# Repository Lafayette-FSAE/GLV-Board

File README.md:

# GLV-Board
Old Rev 4 of GLV Board

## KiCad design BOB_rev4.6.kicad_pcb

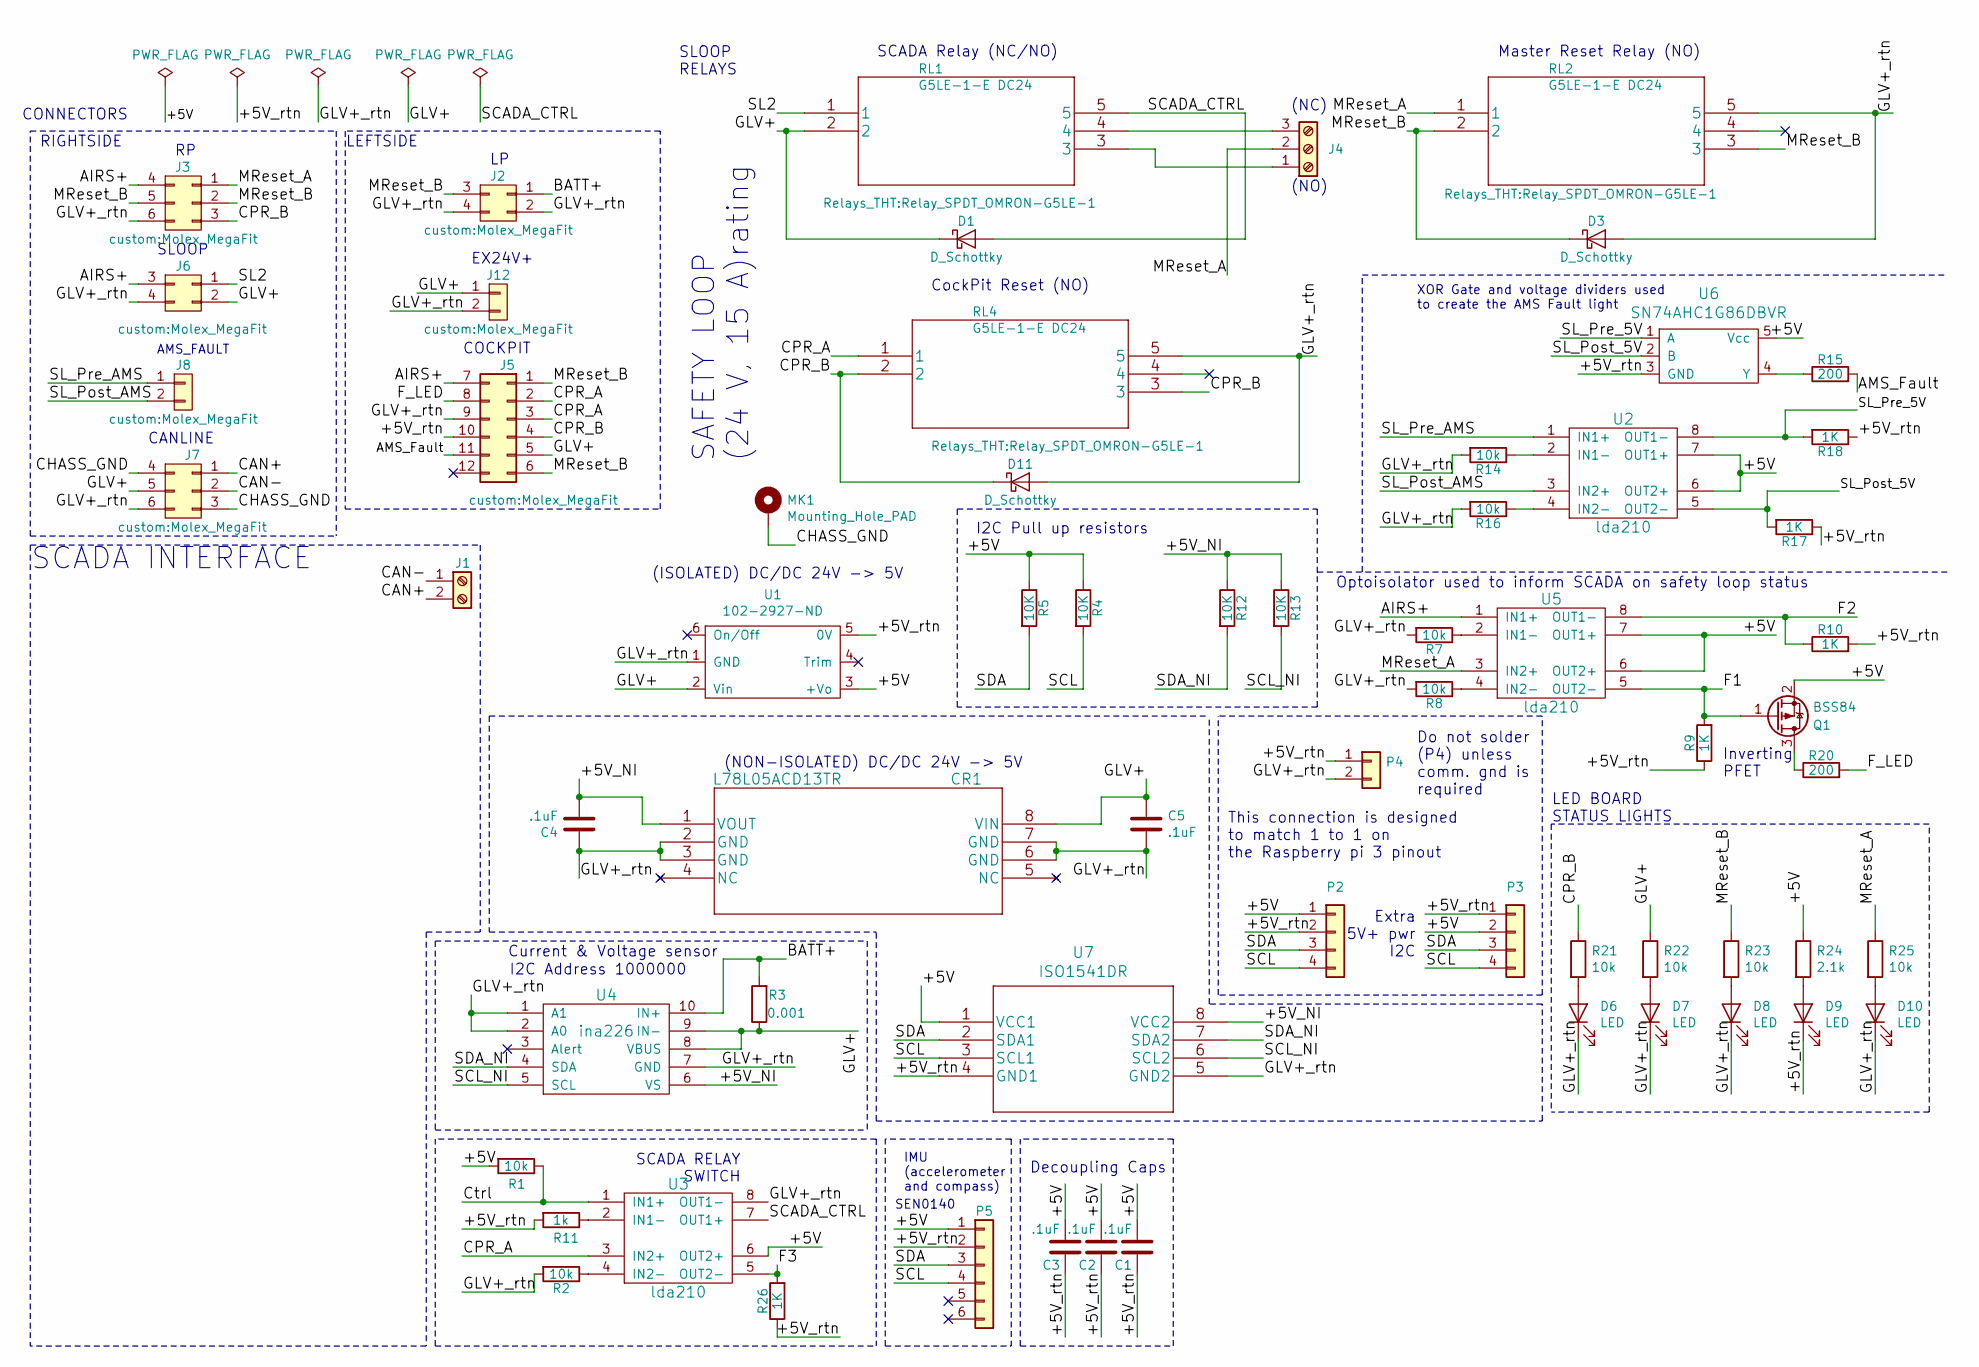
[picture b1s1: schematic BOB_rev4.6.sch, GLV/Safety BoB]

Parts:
C1, C2, C3, C4, C5: .1uF; C_0805_HandSoldering
CR1: L78L05ACD13TR
D1, D3, D11: D_Schottky; D_SMA_Handsoldering
D6, D7, D8, D9, D10: LED; LED_0805
J1: CONN_01X02; TerminalBlock_Pheonix_MPT-5.08mm_2pol
J2: Conn_02x02; Molex_MegaFit
J3: CONN_02X03; Molex_MegaFit
J4: CONN_01X03
J5: CONN_02X06-conn; Molex_MegaFit
J6, J7: Conn_02x03; Molex_MegaFit
J8, J12: Conn_01x02; Molex_MegaFit
MK1: Mounting_Hole_PAD; MountingHole_2.5mm_Pad
P2, P3, P5: CONN_01X04; Socket_Strip_Straight_1x04_Pitch2.54mm
P4: CONN_01X02; Socket_Strip_Straight_2x01_Pitch2.54mm
Q1: BSS84; SOT-23
R1, R2, R7, R8, R14, R16, R21, R22, R23, R25: 10k; R_0805_HandSoldering
R3: 0.001; R_0805_HandSoldering
R4, R5, R12, R13: 10K; R_0805_HandSoldering
R9, R10, R17, R18, R26: 1K; R_0805_HandSoldering
R11: 1k; R_0805_HandSoldering
R15, R20: 200; R_0805_HandSoldering
R24: 2.1k; R_0805_HandSoldering
RL1, RL2, RL4: G5LE-1-E DC24; Relay_SPDT_OMRON-G5LE-1
U1: 102-2927-ND
U2, U3, U5: lda210; DIP-8_W7.62mm
U4: ina226; msop_10_ads1015
U6: SN74AHC1G86DBVR; SOT-23-5_HandSoldering
U7: ISO1541DR

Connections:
/+5V: C1.2, C2.2, C3.2, P2.1, P3.2, P5.1, Q1.2 (S), R1.2, R4.1, R5.1, R24.1, U1.3 (+Vo), U2.6 (OUT2+), U2.7 (OUT1+), U3.6 (OUT2+), U5.6 (OUT2+), U5.7 (OUT1+), U6.5 (Vcc), U7.1 (VCC1)
/+5V_NI: C4.2, CR1.1 (VOUT), R12.1, R13.1, U4.6 (VS), U7.8 (VCC2)
/+5V_rtn: C1.1, C2.1, C3.1, D9.1 (K), J5.10, P2.2, P3.1, P4.1, P5.2, R9.1, R10.2, R11.2, R17.1, R18.1, R26.1, U1.5 (0V), U6.3 (GND), U7.4 (GND1)
/AIRS+: J3.4, J5.7, J6.3, U5.1 (IN1+)
/AMS_Fault: J5.11, R15.2
/BATT+: J2.1, R3.2, U4.10 (IN+)
/CAN+: J1.2, J7.1
/CAN-: J1.1, J7.2
/CHASS_GND: J7.3, J7.4, MK1.1
/CPR_A: J5.2, J5.3, RL4.1, U3.3 (IN2+)
/CPR_B: D11.1 (K), J3.3, J5.4, R21.1, RL4.2, RL4.3
/Ctrl: R1.1, U3.1 (IN1+)
/F1: Q1.1 (G), R9.2, U5.5 (OUT2-)
/F2: R10.1, U5.8 (OUT1-)
/F3: R26.2, U3.5 (OUT2-)
/F_LED: J5.8, R20.2
/GLV+: C5.1, CR1.8 (VIN), D1.1 (K), J5.5, J6.2, J7.5, J12.1, R3.1, R22.1, RL1.2, U1.2 (Vin), U4.8 (VBUS), U4.9 (IN-)
/GLV+_rtn: C4.1, C5.2, CR1.2 (GND), CR1.3 (GND), CR1.6 (GND), CR1.7 (GND), D3.2 (A), D6.1 (K), D7.1 (K), D8.1 (K), D10.1 (K), D11.2 (A), J2.2, J2.4, J3.6, J5.9, J6.4, J7.6, J12.2, P4.2, R2.2, R7.2, R8.2, R14.2, R16.2, RL2.5, RL4.5, U1.1 (GND), U3.8 (OUT1-), U4.1 (A1), U4.2 (A0), U4.7 (GND), U7.5 (GND2)
/MReset_A: J3.1, J4.2, R25.1, RL2.1, U5.3 (IN2+)
/MReset_B: D3.1 (K), J2.3, J3.2, J3.5, J5.1, J5.6, R23.1, RL2.2, RL2.3
/SCADA_CTRL: D1.2 (A), RL1.5, U3.7 (OUT1+)
/SCL: P2.4, P3.4, P5.4, R4.2, U7.3 (SCL1)
/SCL_NI: R13.2, U4.5 (SCL), U7.6 (SCL2)
/SDA: P2.3, P3.3, P5.3, R5.2, U7.2 (SDA1)
/SDA_NI: R12.2, U4.4 (SDA), U7.7 (SDA2)
/SL2: J6.1, RL1.1
/SL_Post_5V: R17.2, U2.5 (OUT2-), U6.2 (B)
/SL_Post_AMS: J8.2, U2.3 (IN2+)
/SL_Pre_5V: R18.2, U2.8 (OUT1-), U6.1 (A)
/SL_Pre_AMS: J8.1, U2.1 (IN1+)
unnamed: D6.2 (A), R21.2
unnamed: D7.2 (A), R22.2
unnamed: D8.2 (A), R23.2
unnamed: D9.2 (A), R24.2
unnamed: D10.2 (A), R25.2
unnamed: J4.1, RL1.3
unnamed: J4.3, RL1.4
unnamed: Q1.3 (D), R20.1
unnamed: R2.1, U3.4 (IN2-)
unnamed: R7.1, U5.2 (IN1-)
unnamed: R8.1, U5.4 (IN2-)
unnamed: R11.1, U3.2 (IN1-)
unnamed: R14.1, U2.2 (IN1-)
unnamed: R15.1, U6.4 (Y)
unnamed: R16.1, U2.4 (IN2-)

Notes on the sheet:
Optoisolator used to inform SCADA on safety loop status
I2C Pull up resistors
Master Reset Relay (NO)
SCADA Relay (NC/NO)
CockPit Reset (NO)
Decoupling Caps
SLOOP
EX24V+
Extra 5V+ pwr I2C
LED BOARD STATUS LIGHTS
SLOOP RELAYS
CONNECTORS
RIGHTSIDE
COCKPIT
SCADA INTERFACE
This connection is designed to match 1 to 1 on the Raspberry pi 3 pinout
(NC)
(NO)
SAFETY LOOP (24 V, 15 A)rating
(NON-ISOLATED) DC/DC 24V -> 5V
SCADA RELAY SWITCH
Current & Voltage sensor
I2C Address 1000000
IMU (accelerometer and compass)
XOR Gate and voltage dividers used to create the AMS Fault light
(ISOLATED) DC/DC 24V -> 5V
SEN0140
AMS_FAULT
Do not solder (P4) unless comm. gnd is required
Inverting PFET
CANLINE
LEFTSIDE

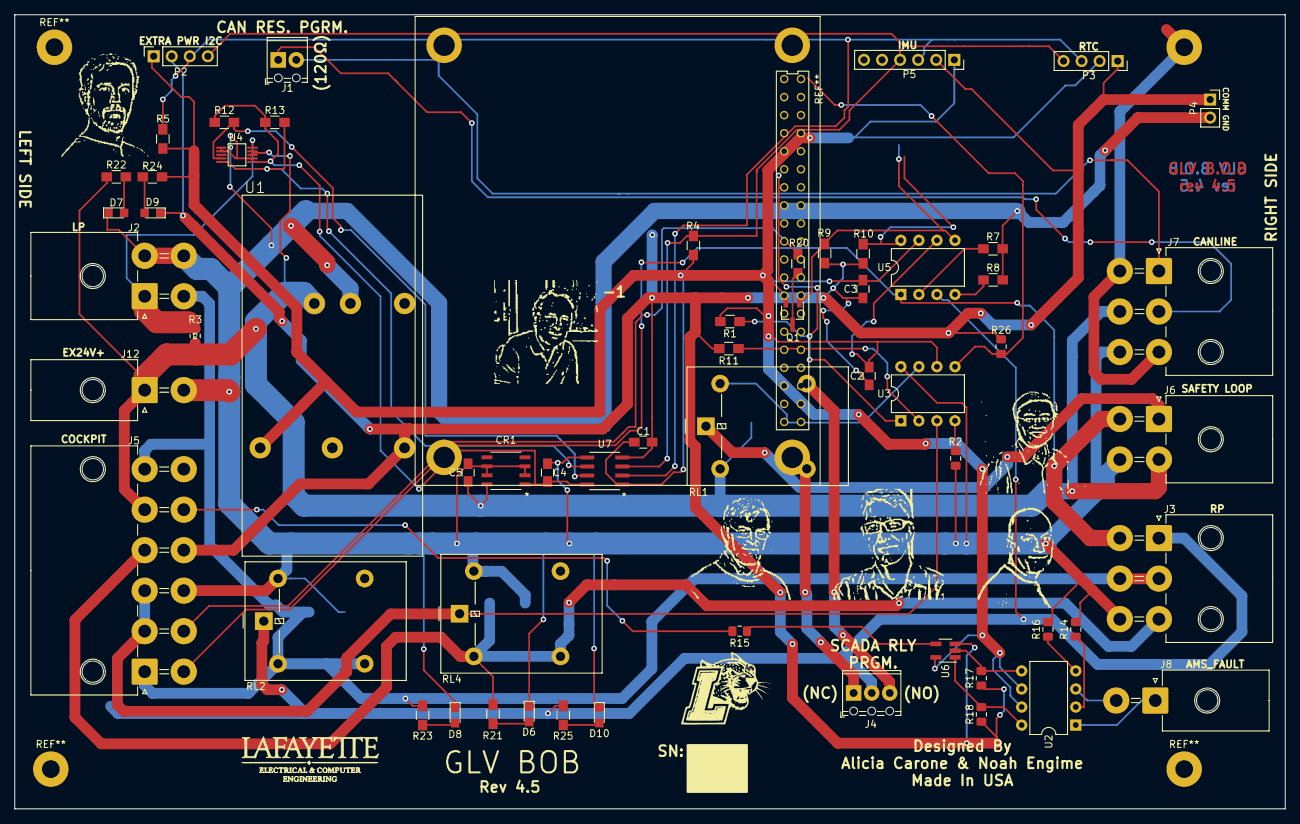
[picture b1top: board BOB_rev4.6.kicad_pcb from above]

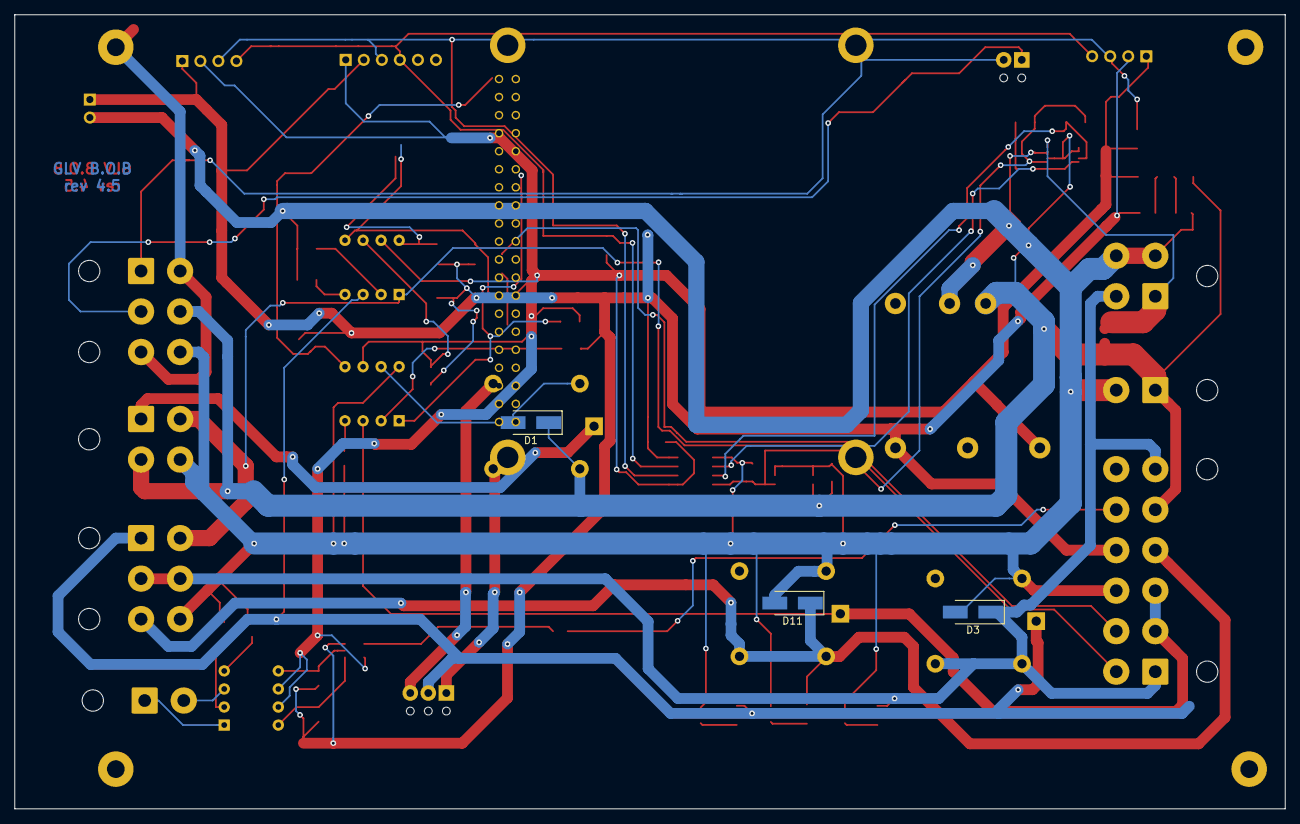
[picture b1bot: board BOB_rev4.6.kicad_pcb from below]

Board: 2 copper layers, 178.8 x 111.8 mm, 69 parts (3 on the bottom side), 45 nets.

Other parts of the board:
LOGO: LOGO
nadovich: nadovich
nestor: nestor
wallace: wallace
wey: wey
yu: yu

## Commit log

2020-02-25 Adding Board to Git

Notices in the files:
parts and their libraries:
Copyright 2016 Accelerated Designs. All rights reserved.
